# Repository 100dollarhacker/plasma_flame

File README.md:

This project contains EAGLE files, with those files you can create our own board. 
The some of the values in the schematics are incorect, some of the values were 
choosen to better fit PCB geometry.

Please use values and types of the components as explaint in 
https://www.youtube.com/watch?v=Rm9mDJxE2Yw

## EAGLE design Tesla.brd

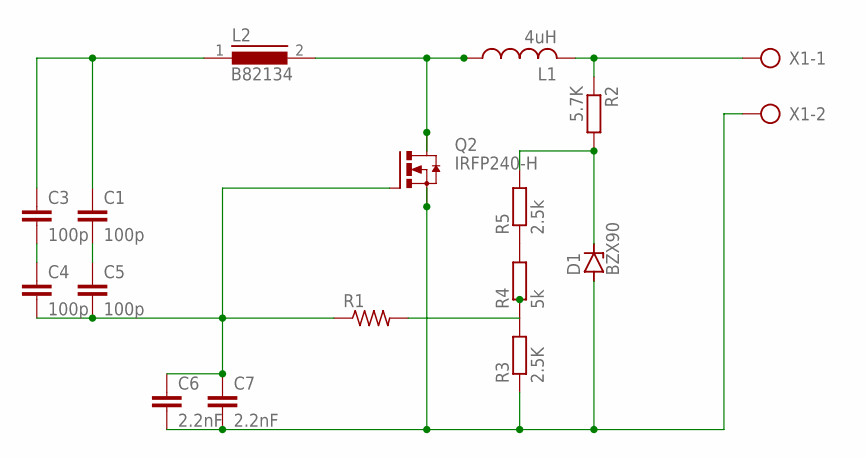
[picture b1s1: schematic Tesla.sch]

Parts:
C1, C3, C4, C5: 100p; C15B5
C6, C7: 2.2nF; C15B5
D1: BZX90; DO34Z7
L1: 4uH; TFI0510
L2: B82134; SUKW4-32
Q2: IRFP240-H; TO247BH
R1: R-US_0309/12; 0309/12
R2: 5.7K; 0204/7
R3: 2.5K; 0204/7
R4: 5k; 0204/7
R5: 2.5k; 0204/7
X1: AK300/2

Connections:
GND: C6.2, C7.2, D1.A, Q2.S, R3.1, X1.2
unnamed: L1.2, R2.1, X1.1
unnamed: R4.2, R5.1
unnamed: C1.1, C3.1, L2.1
unnamed: C3.2, C4.1
unnamed: C1.2, C5.1
unnamed: L1.1, L2.2, Q2.D
unnamed: D1.C, R2.2, R5.2
unnamed: R1.2, R3.2, R4.1
unnamed: C4.2, C5.2, C6.1, C7.1, Q2.G, R1.1

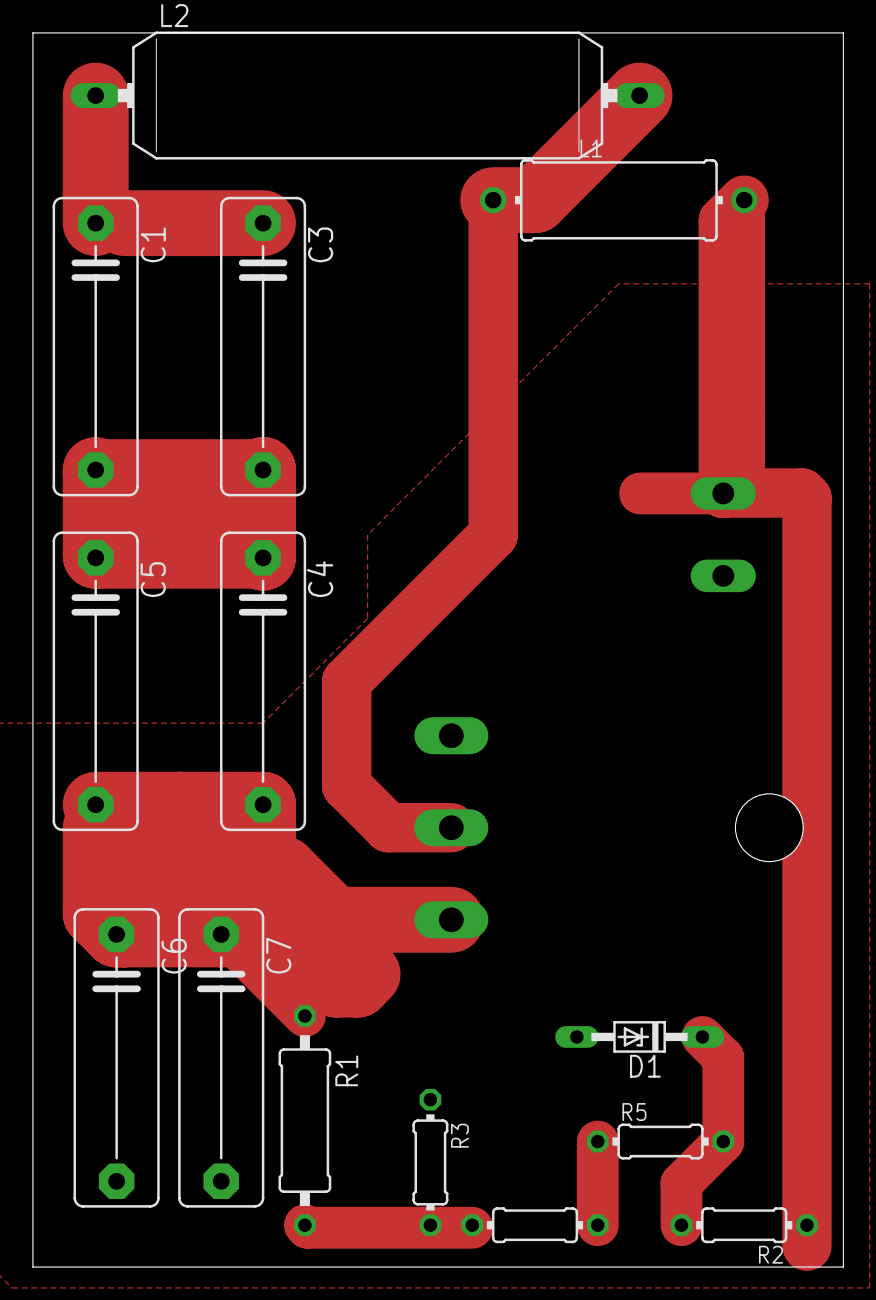
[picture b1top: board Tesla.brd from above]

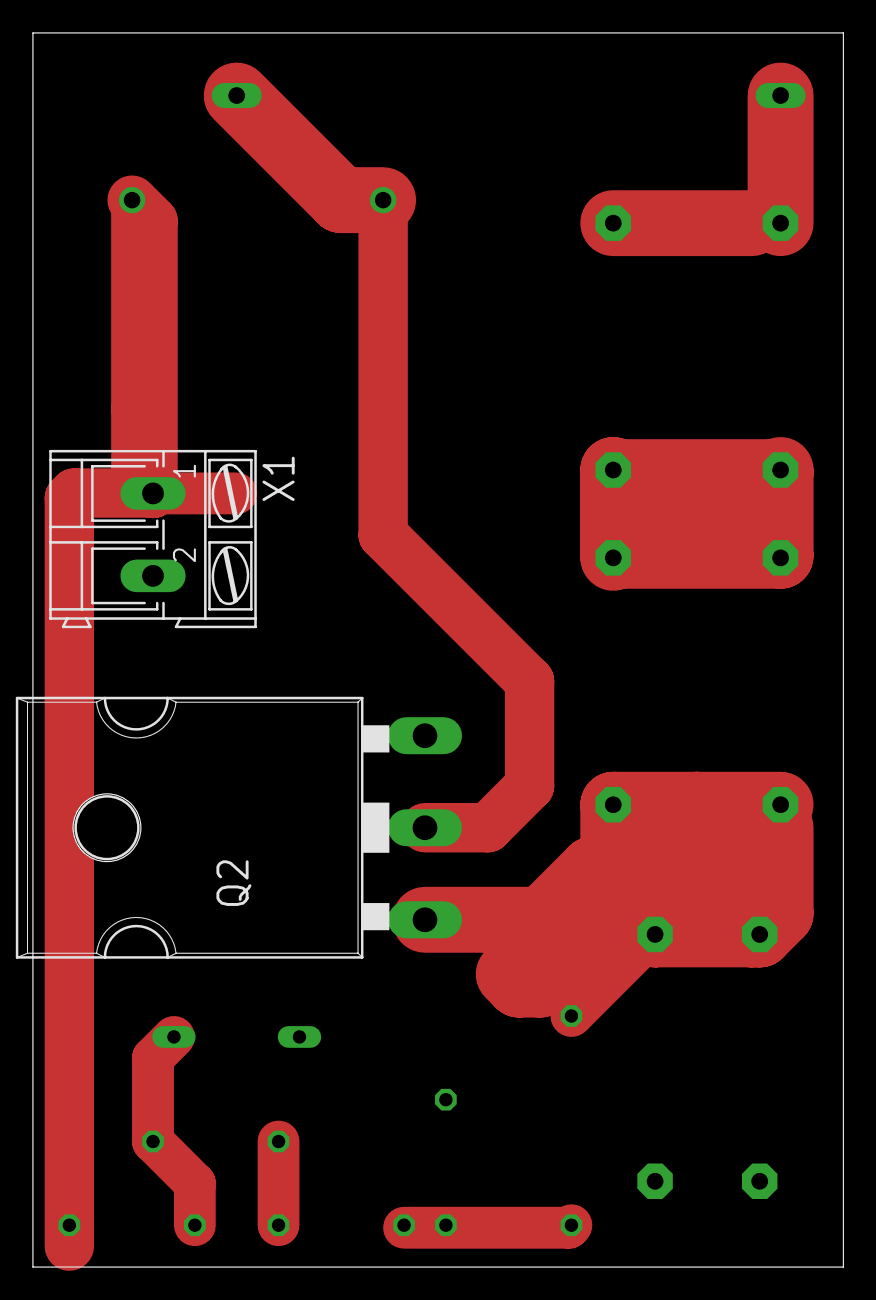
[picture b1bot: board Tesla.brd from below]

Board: 2 copper layers, 49.2 x 74.9 mm, 16 parts (2 on the bottom side), 10 nets.

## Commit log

2023-07-20 Board and schematic
2023-09-26 Si5351 code added
